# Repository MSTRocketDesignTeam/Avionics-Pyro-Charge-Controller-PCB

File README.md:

# Pyro-Charge-Controller-PCB
KiCAD PCB files of rocket board designed to handle interactions with external pyro charges

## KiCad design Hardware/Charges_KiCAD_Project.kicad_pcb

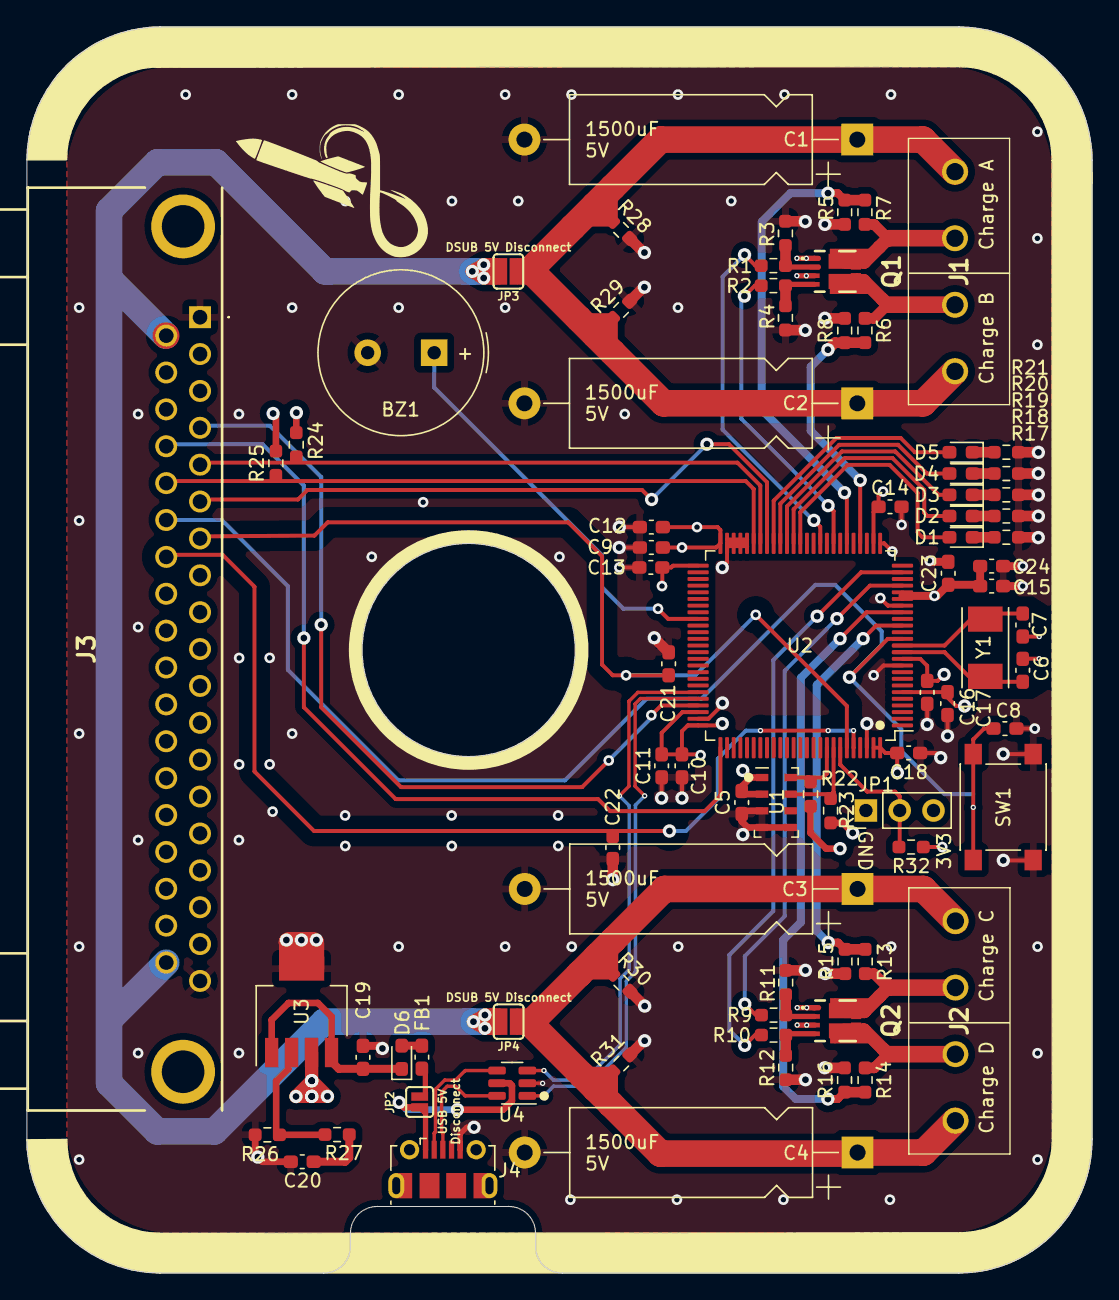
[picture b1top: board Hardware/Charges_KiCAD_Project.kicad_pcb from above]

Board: 4 copper layers, 80.0 x 93.6 mm, 80 parts (0 on the bottom side), 54 nets.

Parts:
BZ1: TP124005-2; Buzzer_TDK_PS1240P02BT_D12.2mm_H6.5mm
C1, C2, C3, C4: 1500uF; CP_Axial_L18.0mm_D6.5mm_P25.00mm_Horizontal
C5, C8, C10, C11, C12, C13, C14, C15, C16, C17, C18, C21, C22: 100nF; C_0603_1608Metric_Pad1.08x0.95mm_HandSolder
C6, C7: 30pF; C_0603_1608Metric_Pad1.08x0.95mm_HandSolder
C9, C20, C23, C24: 1uF; C_0603_1608Metric_Pad1.08x0.95mm_HandSolder
C19: 0.1uF; C_0603_1608Metric_Pad1.08x0.95mm_HandSolder
D1, D3, D5: Red; LED_0603_1608Metric_Pad1.05x0.95mm_HandSolder
D2, D4: Grn; LED_0603_1608Metric_Pad1.05x0.95mm_HandSolder
D6: D_Schottky_Small; D_0603_1608Metric_Pad1.05x0.95mm_HandSolder
FB1: Ferrite_Bead_Small; C_0603_1608Metric_Pad1.08x0.95mm_HandSolder
J1, J2: Terminal Block; TB00250004BE
J3: DB37_Male_MountingHoles; L717SDC37P1ACH4F
J4: 10118192-0001LF; USB_Micro-B_Molex-105017-0001
JP1: Debug Jumper; PinHeader_1x03_P2.54mm_Vertical
JP2: USB 5V Disconnect; SMT-JUMPER_2_NO_SILK
JP3, JP4: DSUB 5V Disconnect; SMT-JUMPER_2_NO_SILK
Q1, Q2: SI7232DN-T1-GE3; SI7232DNT1GE3
R1, R2, R9, R10: 1k; R_0603_1608Metric_Pad0.98x0.95mm_HandSolder
R3, R4, R11, R12, R28, R29, R30, R31: 10k; R_0603_1608Metric_Pad0.98x0.95mm_HandSolder
R5, R6, R13, R14: 100k; R_0603_1608Metric_Pad0.98x0.95mm_HandSolder
R7, R8, R15, R16: 27k; R_0603_1608Metric_Pad0.98x0.95mm_HandSolder
R17, R18, R19, R20, R21: 820; R_0603_1608Metric_Pad0.98x0.95mm_HandSolder
R22, R23, R24, R25, R32: 4.7k; R_0603_1608Metric_Pad0.98x0.95mm_HandSolder
R26: 390; R_0603_1608Metric_Pad0.98x0.95mm_HandSolder
R27: 240; R_0603_1608Metric_Pad0.98x0.95mm_HandSolder
SW1: MCU Reset; SW_SPST_PTS645
U1: MS5607-02BA; LGA-8_3x5mm_P1.25mm
U2: STM32L562VET6Q; LQFP-100_14x14mm_P0.5mm
U3: LP38692MPX-ADJ; SOT-223-5
U4: USBLC6-2SC6; SOT-23-6
Y1: 32MHz; XTAL_ABM7-32.000MHZ-D2Y-T

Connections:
+3V3: C5.2, C9.1, C10.1, C11.1, C12.1, C13.1, C14.1, C15.1, C16.1, C17.1, C18.1, C23.1, C24.1, J3.2, J3.18, JP1.3 (B), R22.2, R23.2, R24.2, R25.2, R32.1, U1.1 (VDD), U1.2 (PS), U2.6 (VBAT), U2.11 (VDD), U2.20 (VREF+), U2.21 (VDDA), U2.27 (VDD), U2.50 (V15SMPS_1), U2.51 (VDD), U2.73 (VDDUSB), U2.75 (VDD), U2.99 (V15SMPS_2), U2.100 (VDD), U3.3 (VOUT)
+5V: C1.1, C2.1, C3.1, C4.1, J1.1, J1.4, J2.1, J2.4, JP3.1 (A), JP4.1 (A), R28.1, R29.1, R30.1, R31.1
/37 Pin DSUB/Alert_Active: J3.6, U2.43 (PE15)
/37 Pin DSUB/Alert_scl: J3.5, R24.1, U2.44 (PB10)
/37 Pin DSUB/Alert_sda: J3.24, R25.1, U2.45 (PB11)
/37 Pin DSUB/DSUB-5V: J3.20, J3.37, JP3.2 (B), JP4.2 (B)
/37 Pin DSUB/Fire: C21.2, J3.7, U2.95 (PB8)
/37 Pin DSUB/Fire_redundant: C22.2, J3.26, U2.96 (PB9)
/37 Pin DSUB/SWCLK: J3.23, U2.76 (PA14)
/37 Pin DSUB/SWDIO: J3.4, U2.72 (PA13)
/Barometer_MS5607/SCLK: R22.1, U1.8 (SCLK), U2.92 (PB6)
/Barometer_MS5607/SDI_SDA: R23.1, U1.7 (SDI/SDA), U2.93 (PB7)
/Fire_A: R1.1, U2.35 (PE7)
/Fire_B: R2.1, U2.33 (PB1)
/Fire_C: R9.1, U2.22 (PA0)
/Fire_D: R10.1, U2.24 (PA2)
/Igniter A: J1.2, Q1.7 (D1_1), Q1.8 (D1_2), Q1.9 (D1_3), Q1.10 (D1_4), Q1.11 (D1_5), Q1.15 (D1_6), R5.1
/Igniter B: J1.3, Q1.5 (D2_1), Q1.6 (D2_2), Q1.12 (D2_3), Q1.13 (D2_4), Q1.14 (D2_5), Q1.16 (D2_6), R6.1
/Igniter C: J2.2, Q2.7 (D1_1), Q2.8 (D1_2), Q2.9 (D1_3), Q2.10 (D1_4), Q2.11 (D1_5), Q2.15 (D1_6), R13.1
/Igniter D: J2.3, Q2.5 (D2_1), Q2.6 (D2_2), Q2.12 (D2_3), Q2.13 (D2_4), Q2.14 (D2_5), Q2.16 (D2_6), R14.1
/MCU L562VET6Q/Buzzer: BZ1.1, U2.59 (PD12)
/MCU L562VET6Q/USB_D+: U2.71 (PA12), U4.1 (IO1)
/MCU L562VET6Q/USB_D-: U2.70 (PA11), U4.3 (IO2)
/MCU L562VET6Q/~RESET: C8.1, J3.25, SW1.1, U2.14 (NRST)
/Sense_A: R5.2, R7.1, U2.31 (PA7)
/Sense_B: R6.2, R8.1, U2.29 (PA5)
/Sense_C: R13.2, R15.1, U2.16 (PC1)
/Sense_D: R14.2, R16.1, U2.18 (PC3)
/USB Connector and ESD/USB_5V: J4.1, JP2.1 (A), U4.5 (VBUS)
/USB Connector and ESD/USB_CONN_D+: J4.3, U4.6 (IO1)
/USB Connector and ESD/USB_CONN_D-: J4.2, U4.4 (IO2)
GND: BZ1.2, C1.2, C2.2, C3.2, C4.2, C5.1, C6.2, C7.2, C8.2, C9.2, C10.2, C11.2, C12.2, C13.2, C14.2, C15.2, C16.2, C17.2, C18.2, C19.2, C20.2, C21.1, C22.1, C23.2, C24.2, J3.1, J3.19, J4.5, JP1.1 (A), Q1.1 (S1), Q1.3 (S2), Q2.1 (S1), Q2.3 (S2), R3.2, R4.2, R7.2, R8.2, R11.2, R12.2, R15.2, R16.2, R17.1, R18.1, R19.1, R20.1, R21.1, R26.2, R28.2, R29.2, R30.2, R31.2, SW1.2, U1.3 (GND), U1.4 (CSB), U1.5 (CSB), U2.10 (VSS), U2.19 (VREF-/VSSA), U2.26 (VSS), U2.46 (VDDSMPS), U2.47 (VLXSMPS), U2.48 (VSSSMPS), U2.49 (VSS), U2.74 (VSS), U2.98 (VSS), U3.5 (GND), U4.2 (GND)
unnamed: C6.1, U2.12 (PH0), Y1.1
unnamed: C7.1, U2.13 (PH1), Y1.2
unnamed: C19.1, D6.1 (K), U3.1 (EN), U3.4 (VIN)
unnamed: C20.1, R27.1
unnamed: D1.1 (K), R17.2
unnamed: D1.2 (A), U2.38 (PE10)
unnamed: D2.1 (K), R18.2
unnamed: D2.2 (A), U2.39 (PE11)
unnamed: D3.1 (K), R19.2
unnamed: D3.2 (A), U2.40 (PE12)
unnamed: D4.1 (K), R20.2
unnamed: D4.2 (A), U2.41 (PE13)
unnamed: D5.1 (K), R21.2
unnamed: D5.2 (A), U2.42 (PE14)
unnamed: D6.2 (A), FB1.1
unnamed: FB1.2, JP2.2 (B)
unnamed: JP1.2 (C), R32.2, U2.94 (PH3)
unnamed: Q1.2 (G1), R1.2, R3.1
unnamed: Q1.4 (G2), R2.2, R4.1
unnamed: Q2.2 (G1), R9.2, R11.1
unnamed: Q2.4 (G2), R10.2, R12.1
unnamed: R26.1, R27.2, U3.2 (ADJ)

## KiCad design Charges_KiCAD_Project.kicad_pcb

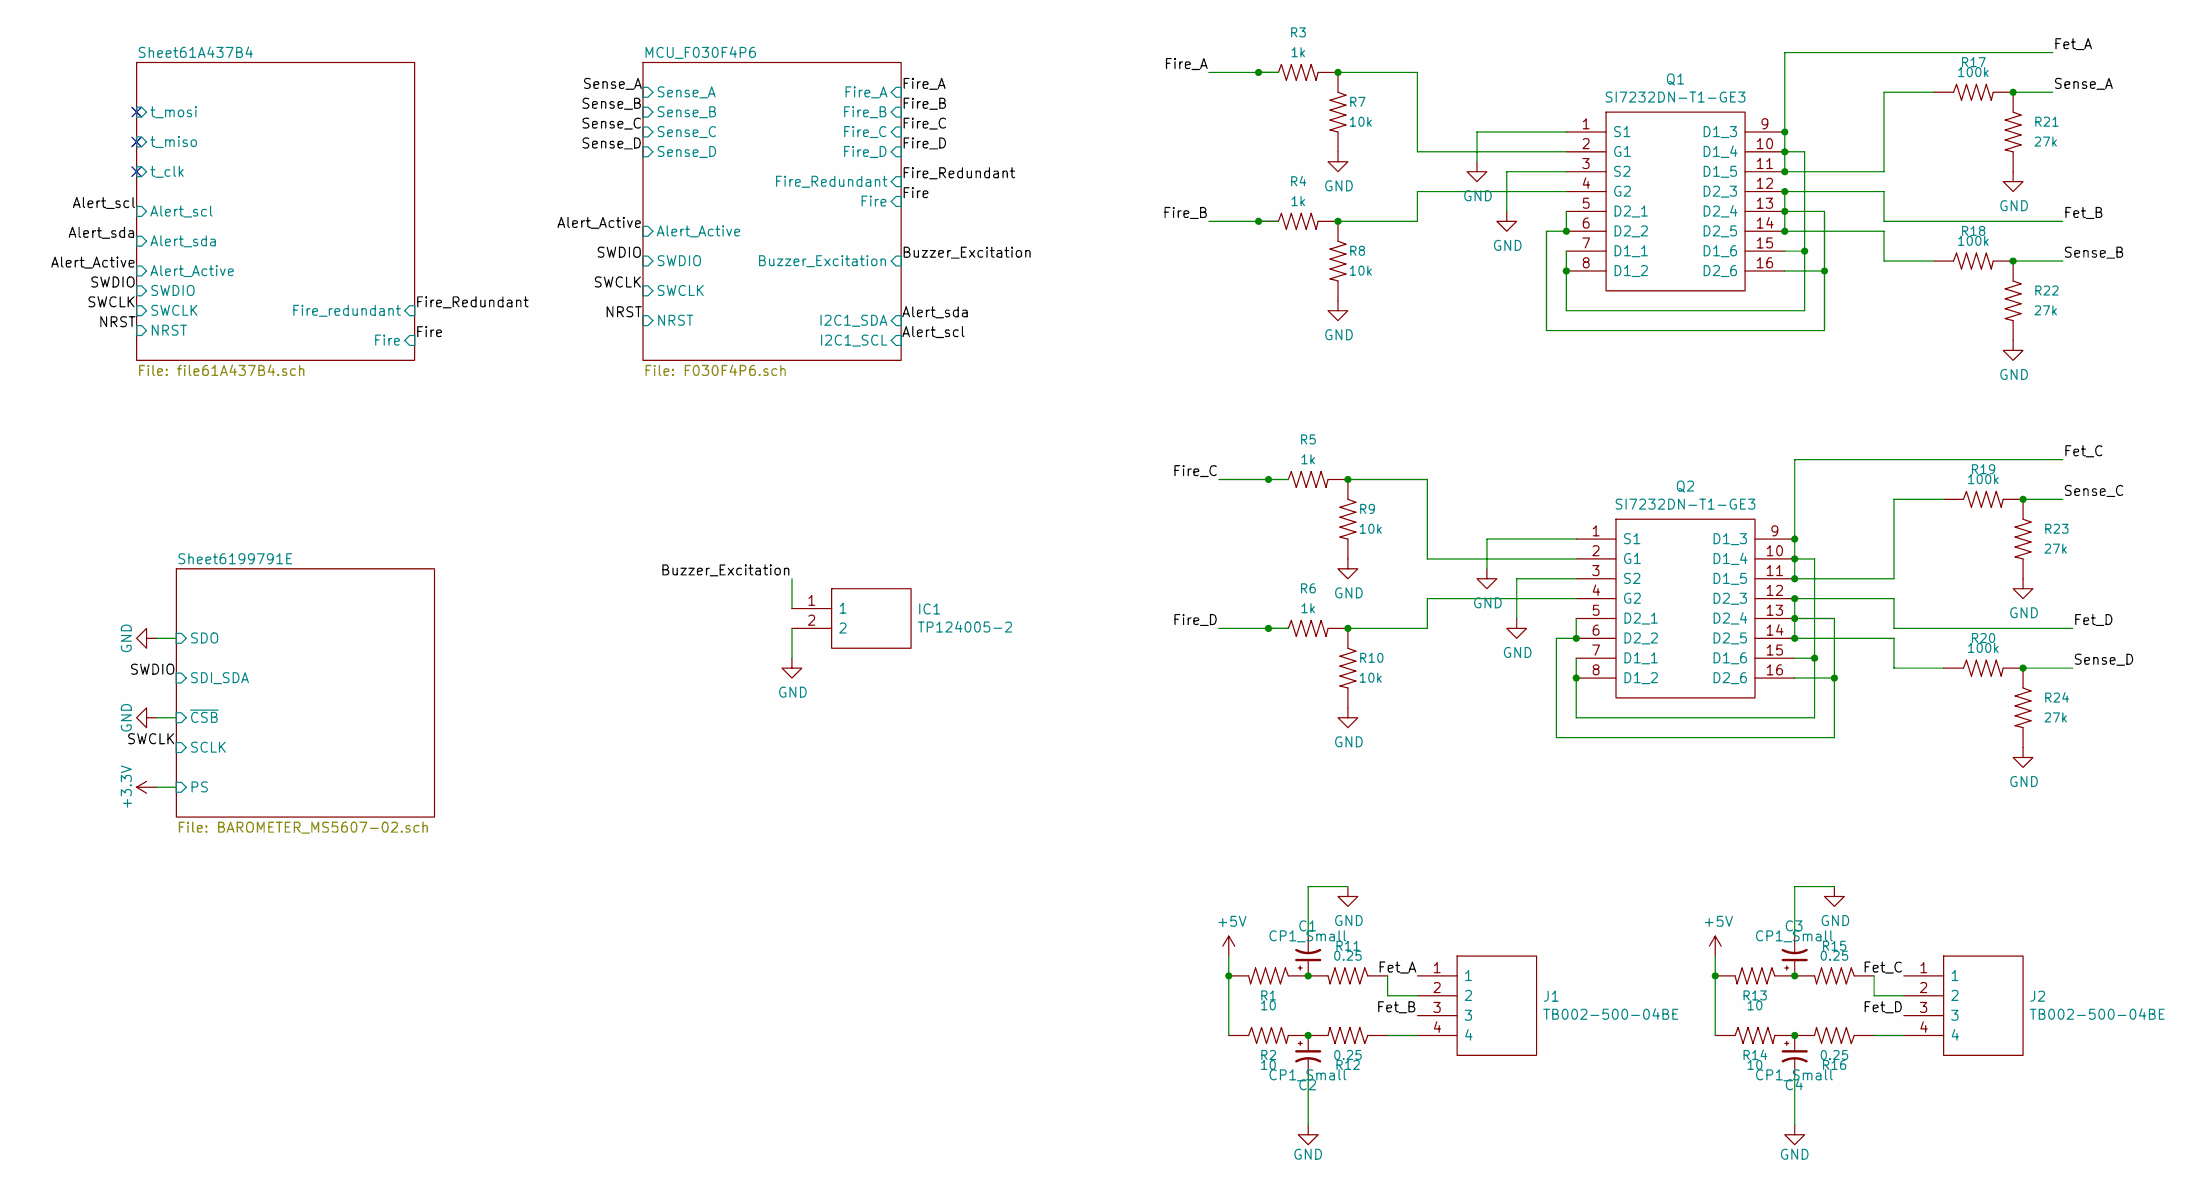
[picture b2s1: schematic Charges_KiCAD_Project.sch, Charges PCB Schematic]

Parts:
C1, C2, C3, C4: CP1_Small; CP_Axial_L10.0mm_D4.5mm_P15.00mm_Horizontal
IC1: TP124005-2; TP1240052; Mouser Part Number 497-TP124005-2
J1, J2: TB002-500-04BE; TB00250004BE; Mouser Part Number 490-TB002-500-04BE
Q1, Q2: SI7232DN-T1-GE3; SI7232DNT1GE3; Mouser Part Number 781-SI7232DN-GE3
R1, R2, R13, R14: 10; R_0603_1608Metric
R3, R4, R5, R6: 1k; R_0603_1608Metric
R7, R8, R9, R10: 10k; R_0603_1608Metric
R11, R12, R15, R16: 0.25; R_0603_1608Metric
R17, R18, R19, R20: 100k; R_0603_1608Metric
R21, R22, R23, R24: 27k; R_0603_1608Metric

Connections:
+5V: R1.2, R2.1, R13.2, R14.1; also elsewhere on the board
/Buzzer_Excitation: IC1.1; also elsewhere on the board
/Fet_A: J1.1, Q1.7 (D1_1), Q1.8 (D1_2), Q1.9 (D1_3), Q1.10 (D1_4), Q1.11 (D1_5), Q1.15 (D1_6), R17.1
/Fet_B: J1.3, Q1.5 (D2_1), Q1.6 (D2_2), Q1.12 (D2_3), Q1.13 (D2_4), Q1.14 (D2_5), Q1.16 (D2_6), R18.1
/Fet_C: J2.1, Q2.7 (D1_1), Q2.8 (D1_2), Q2.9 (D1_3), Q2.10 (D1_4), Q2.11 (D1_5), Q2.15 (D1_6), R19.1
/Fet_D: J2.3, Q2.5 (D2_1), Q2.6 (D2_2), Q2.12 (D2_3), Q2.13 (D2_4), Q2.14 (D2_5), Q2.16 (D2_6), R20.1
/Fire_A: R3.1; also elsewhere on the board
/Fire_B: R4.1; also elsewhere on the board
/Fire_C: R5.1; also elsewhere on the board
/Fire_D: R6.1; also elsewhere on the board
/Sense_A: R17.2, R21.1; also elsewhere on the board
/Sense_B: R18.2, R22.1; also elsewhere on the board
/Sense_C: R19.2, R23.1; also elsewhere on the board
/Sense_D: R20.2, R24.1; also elsewhere on the board
GND: C1.2, C2.2, C3.2, C4.2, IC1.2, Q1.1 (S1), Q1.3 (S2), Q2.1 (S1), Q2.3 (S2), R7.2, R8.2, R9.2, R10.2, R21.2, R22.2, R23.2, R24.2; also elsewhere on the board
unnamed: C1.1, R1.1, R11.2
unnamed: C2.1, R2.2, R12.2
unnamed: C3.1, R13.1, R15.2
unnamed: C4.1, R14.2, R16.2
unnamed: J1.2, R11.1
unnamed: J1.4, R12.1
unnamed: J2.2, R15.1
unnamed: J2.4, R16.1
unnamed: Q1.2 (G1), R3.2, R7.1
unnamed: Q1.4 (G2), R4.2, R8.1
unnamed: Q2.2 (G1), R5.2, R9.1
unnamed: Q2.4 (G2), R6.2, R10.1

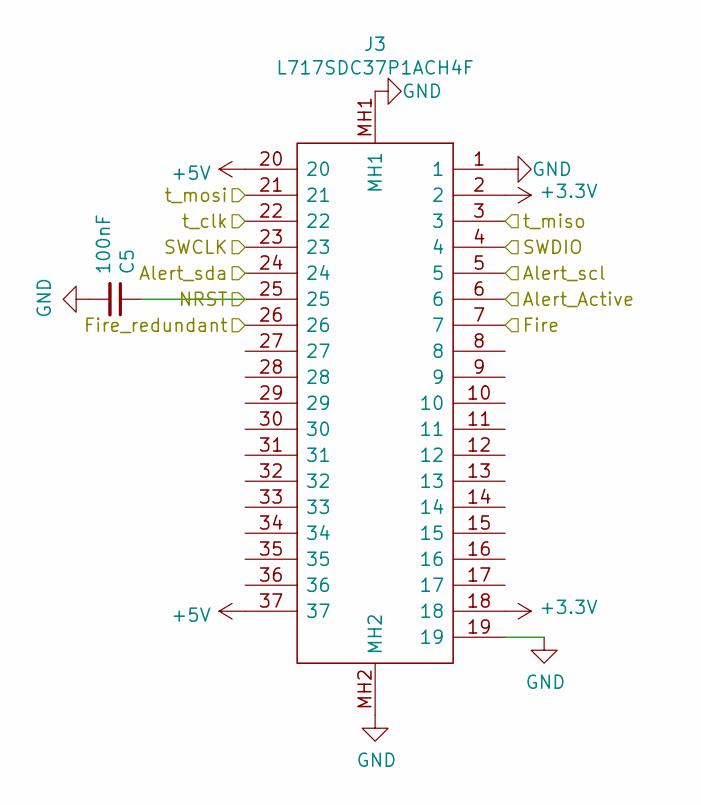
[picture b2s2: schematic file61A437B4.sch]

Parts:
C5: 100nF; C_0603_1608Metric
J3: L717SDC37P1ACH4F; Mouser Part Number 523-L717SDC37P1ACH4F

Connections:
+3V3: J3.2, J3.18; also elsewhere on the board
+5V: J3.20, J3.37; also elsewhere on the board
/Alert_Active: J3.6; also elsewhere on the board
/Alert_scl: J3.5; also elsewhere on the board
/Alert_sda: J3.24; also elsewhere on the board
/Fire: J3.7; also elsewhere on the board
/Fire_Redundant: J3.26; also elsewhere on the board
/NRST: C5.1, J3.25; also elsewhere on the board
/SWCLK: J3.23; also elsewhere on the board
/SWDIO: J3.4; also elsewhere on the board
/Sheet61A437B4/t_clk: J3.22
/Sheet61A437B4/t_miso: J3.3
/Sheet61A437B4/t_mosi: J3.21
GND: C5.2, J3.1, J3.19, J3.MH1, J3.MH2; also elsewhere on the board

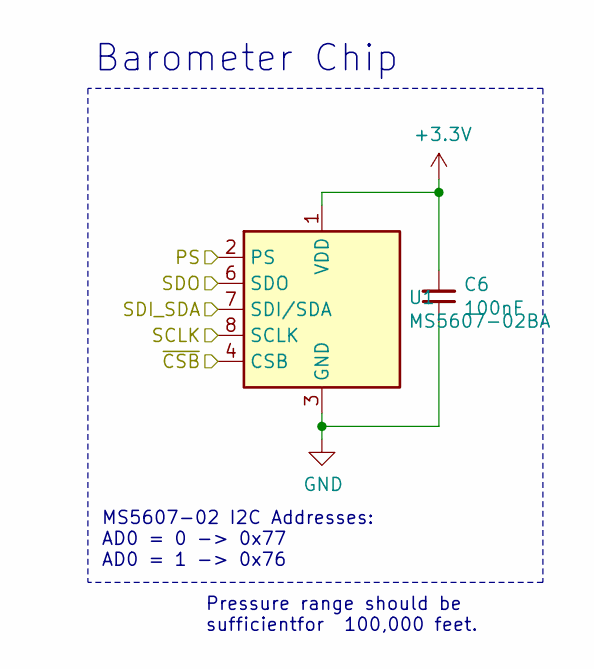
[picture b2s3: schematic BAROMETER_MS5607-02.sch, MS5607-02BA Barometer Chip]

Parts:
C6: 100nF; C_0603_1608Metric
U1: MS5607-02BA; LGA-8_3x5mm_P1.25mm

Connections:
+3V3: C6.2, U1.1 (VDD), U1.2 (PS); also elsewhere on the board
/SWCLK: U1.8 (SCLK); also elsewhere on the board
/SWDIO: U1.7 (SDI/SDA); also elsewhere on the board
GND: C6.1, U1.3 (GND), U1.4 (CSB), U1.5 (CSB), U1.6 (SDO); also elsewhere on the board

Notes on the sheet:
Barometer Chip
MS5607-02 I2C Addresses: AD0 = 0 -> 0x77 AD0 = 1 -> 0x76
Pressure range should be sufficientfor ~ 100,000 feet.

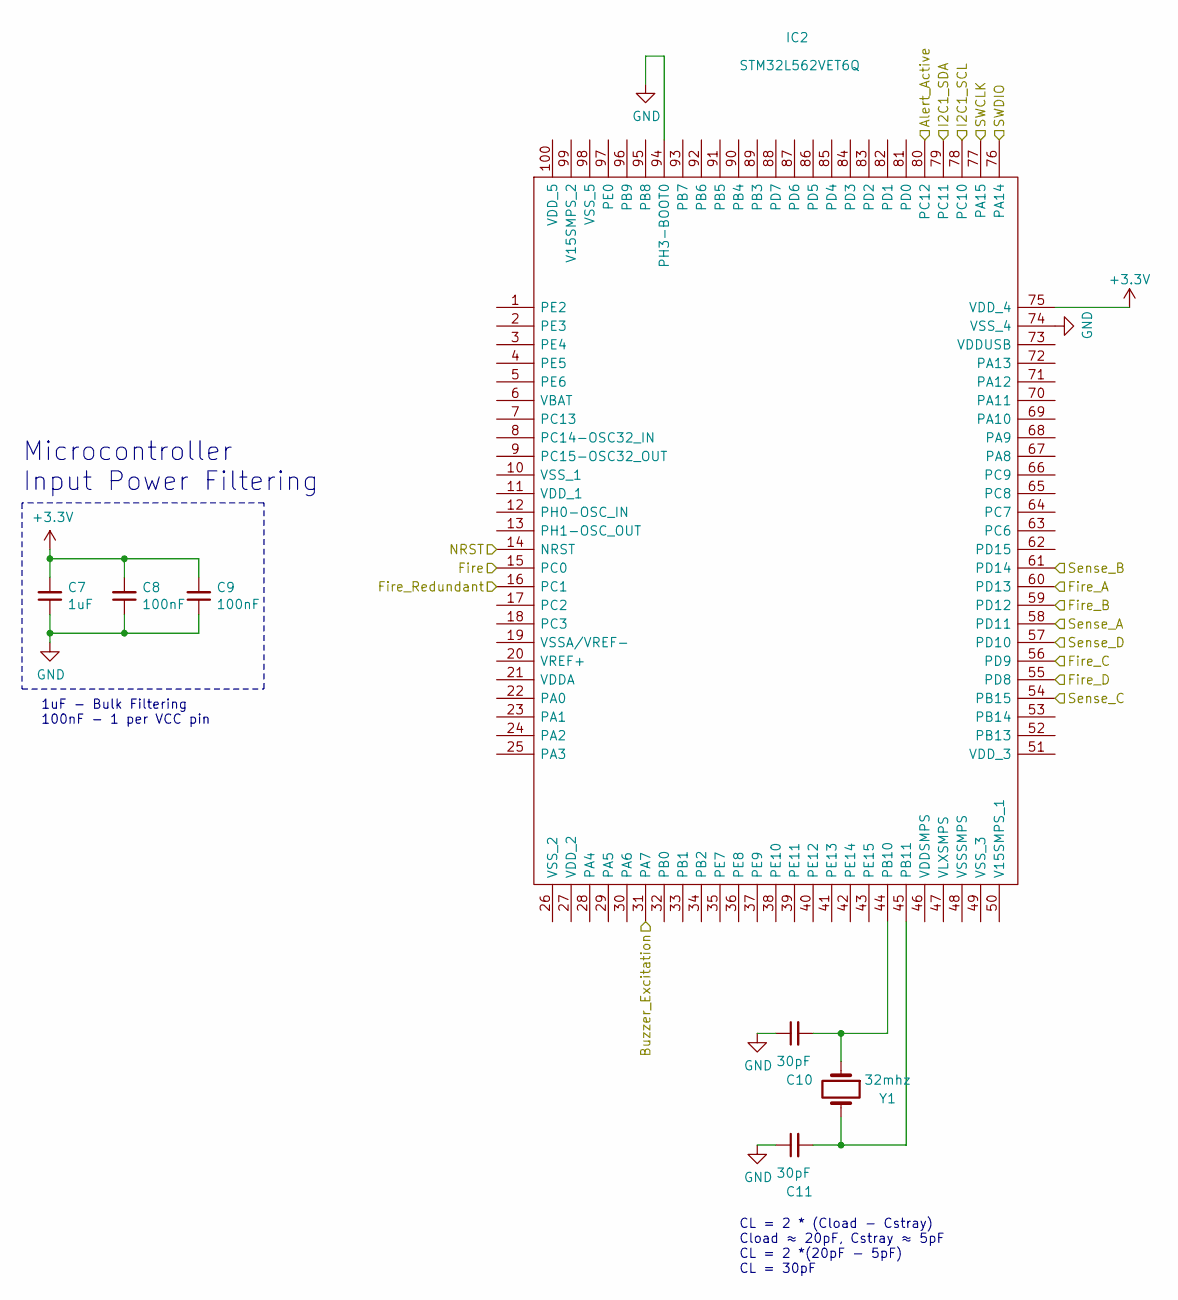
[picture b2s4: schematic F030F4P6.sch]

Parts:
C7: 1uF; C_0603_1608Metric
C8, C9: 100nF; C_0603_1608Metric
C10, C11: 30pF; C_0603_1608Metric
IC2: STM32L562VET6Q; QFP50P1600X1600X160-100N; Mouser Part Number 511-STM32L562VET6Q
Y1: 32mhz; Crystal_HC49-4H_Vertical

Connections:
+3V3: C7.2, C8.2, C9.2, IC2.75 (VDD_4); also elsewhere on the board
/Alert_Active: IC2.80 (PC12); also elsewhere on the board
/Alert_scl: IC2.78 (PC10); also elsewhere on the board
/Alert_sda: IC2.79 (PC11); also elsewhere on the board
/Buzzer_Excitation: IC2.31 (PA7); also elsewhere on the board
/Fire: IC2.15 (PC0); also elsewhere on the board
/Fire_A: IC2.60 (PD13); also elsewhere on the board
/Fire_B: IC2.59 (PD12); also elsewhere on the board
/Fire_C: IC2.56 (PD9); also elsewhere on the board
/Fire_D: IC2.55 (PD8); also elsewhere on the board
/Fire_Redundant: IC2.16 (PC1); also elsewhere on the board
/NRST: IC2.14 (NRST); also elsewhere on the board
/SWCLK: IC2.77 (PA15); also elsewhere on the board
/SWDIO: IC2.76 (PA14); also elsewhere on the board
/Sense_A: IC2.58 (PD11); also elsewhere on the board
/Sense_B: IC2.61 (PD14); also elsewhere on the board
/Sense_C: IC2.54 (PB15); also elsewhere on the board
/Sense_D: IC2.57 (PD10); also elsewhere on the board
GND: C7.1, C8.1, C9.1, C10.1, C11.1, IC2.74 (VSS_4), IC2.94 (PH3-BOOT0); also elsewhere on the board
unnamed: C10.2, IC2.44 (PB10), Y1.1
unnamed: C11.2, IC2.45 (PB11), Y1.2

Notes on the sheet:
CL = 2 * (Cload - Cstray) Cload ≈ 20pF, Cstray ≈ 5pF CL = 2 *(20pF - 5pF) CL = 30pF
1uF - Bulk Filtering 100nF - 1 per VCC pin
Microcontroller Input Power Filtering

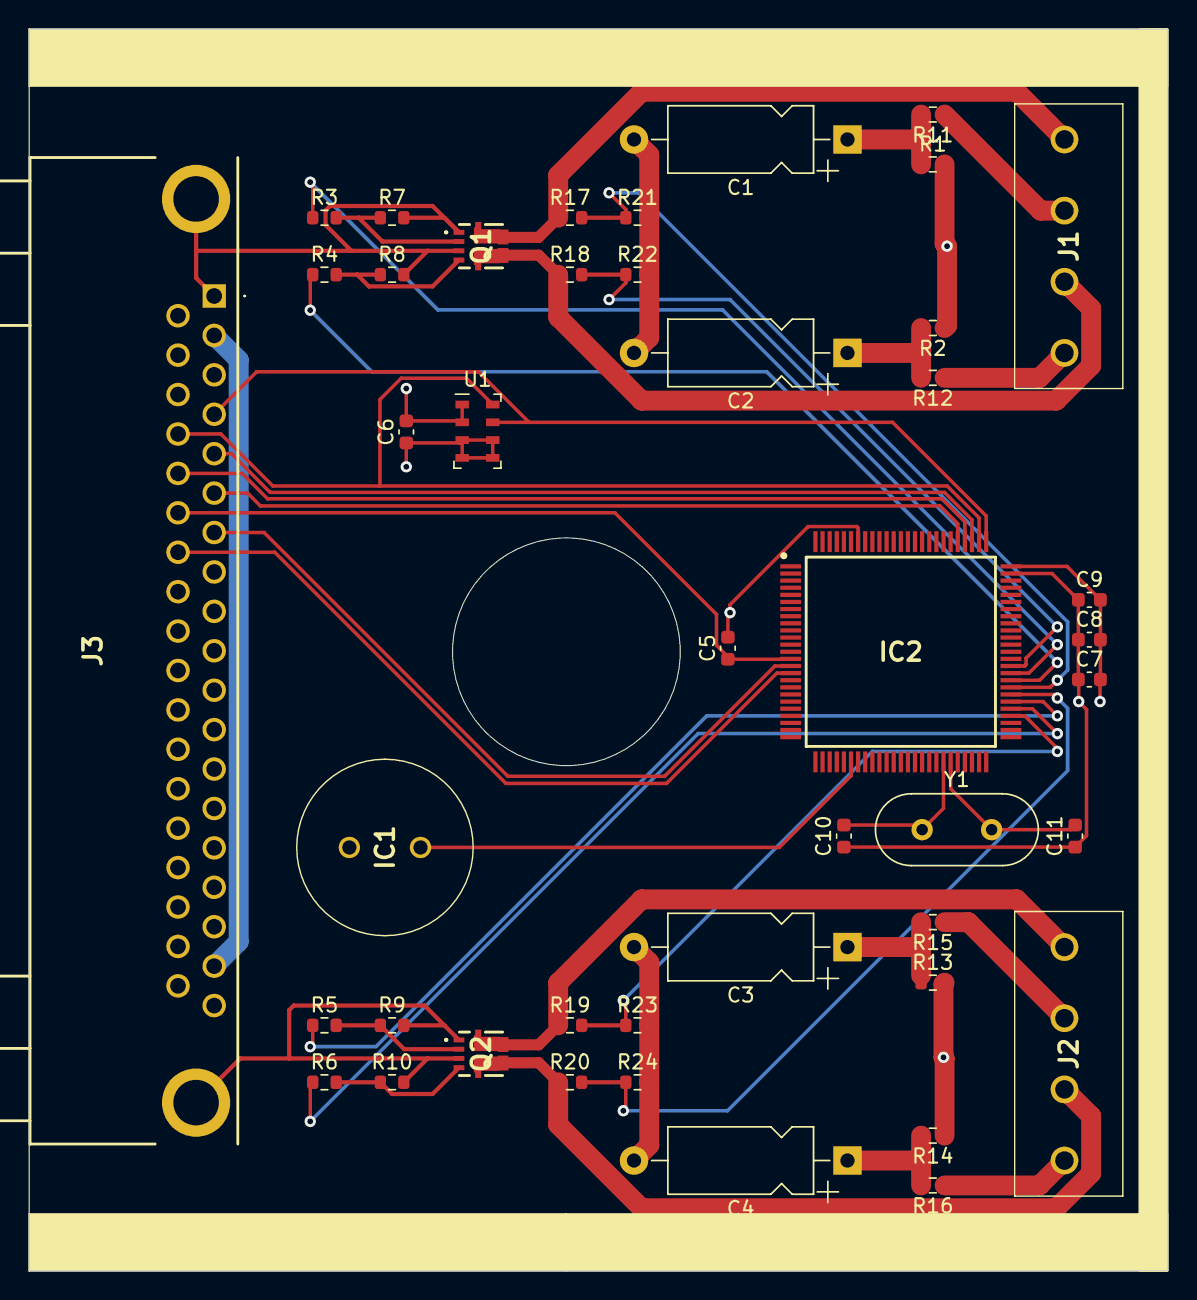
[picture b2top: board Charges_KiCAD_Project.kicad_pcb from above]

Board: 4 copper layers, 80.0 x 87.2 mm, 44 parts (0 on the bottom side), 38 nets.

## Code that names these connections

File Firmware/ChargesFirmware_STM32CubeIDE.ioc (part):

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Mcu.Name=STM32L562VETxQ
Mcu.Package=LQFP100
Mcu.UserName=STM32L562VETxQ
PA11.Mode=Device
PA11.Signal=USB_DM
PA12.Mode=Device
PA12.Signal=USB_DP
PA13\ (JTMS/SWDIO).Mode=Serial_Wire
PA13\ (JTMS/SWDIO).Signal=DEBUG_JTMS-SWDIO
PA14\ (JTCK/SWCLK).Mode=Serial_Wire
PA14\ (JTCK/SWCLK).Signal=DEBUG_JTCK-SWCLK
PB6.Mode=I2C
PB6.Signal=I2C1_SCL
PB7.Mode=I2C
PB7.Signal=I2C1_SDA
PD12.Signal=S_TIM4_CH1
PE14.Signal=GPIO_Output
PH0-OSC_IN\ (PH0).Mode=HSE-External-Oscillator
PH0-OSC_IN\ (PH0).Signal=RCC_OSC_IN
PH1-OSC_OUT\ (PH1).Mode=HSE-External-Oscillator
PH1-OSC_OUT\ (PH1).Signal=RCC_OSC_OUT
RCC.HSE_VALUE=32000000
RCC.SYSCLKFreq_VALUE=96000000
RCC.SYSCLKSource=RCC_SYSCLKSOURCE_PLLCLK
board=custom

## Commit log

2021-09-30 Create LICENSE
2021-11-03 Actually made the boards
    Boards have been made
2021-11-17 Board update
    Added capacitors and extra charge stuff
2021-11-24 Edit to bus
    Bus changed as well as some other things to almost finish it up
2021-11-24 Change to bus
    oopsie on one of the bus pins
2021-11-29 Updated PCB
    Finalized most of the charges board and PCB
2021-11-29 FIx to Via
    Via was too close to a track according to utility. It was moved a bit over.
2021-11-29 Fix to components
    Changed the buzzer and terminal blocks
2021-11-30 updated pcb
    pcb updated to the right size
2021-11-30 Updated PCB
    pcb dimensions were a little off on the silk so that was updated
2021-11-30 added gerber files
    gerber files added
2021-11-30 updated traces
    trace widths were updated
2021-11-30 updated pcb
    pcb wasnt fully aligned. that is now fixed
2021-12-01 updated board
    updated the board again
    added a crystal
2021-12-05 Changes to PCB
    noticed that 3v3 plane only had like 2 connections, so i changed it to a mixed with mainly 5v instead
2021-12-06 Reformatted repo
2021-12-10 Changes to PCB size and components
    PCB size was changed by adding 3mm to the top and bottom, the screw terminal was switched to a 90 degree angle one, and the libraries were updated
2021-12-21 Replaced passive component footprints with handsolder variants
    Most components unaffected, redesign was needed around SI7232DN chips
2021-12-21 Component sheets updated
    Component sheets were added from the telemetry board to match across all boards
2021-12-21 deleting redundant project.
    Project didnt need to be in this folder
2022-01-16 update to caps and board layout
    caps were changed and resistors were removed as they were not needed
2022-01-18 Added qr codes and fixed silk screen
    Qr code was added and the silk screens were fixed. corners were also rounded
2022-01-25 Added signatures to silkscreen
2022-02-04 replaced caps footprint
    footprint for cap was changed and copper pours were on on the top and the bottom
2022-02-04 updated caps
    finished update on cap footprints
2022-02-05 updated traces
    moved traces further away from the center hole
2022-02-05 ignoring backups
    added line to gitignore to ignore the backups on kicad
2022-02-05 Corrected 3D models for buzzer, terminals, mosfets, and mcu
2022-02-07 Added correct crystal for mcu, re-routing of data lines in progress
2022-02-07 Routed Alert I2C lines
2022-02-07 Routed all traces and components, need to place LEDs
2022-02-07 All traces routed
2022-02-07 Added 3D models for USB components
    USB Voltage Regulator chip still needs corrected footprint/pinout
2022-02-07 Realigned pcb grid, added QR code to silkscreen
2022-02-07 Added stitching vias to ground pours
2022-02-07 Adjusted silkscreen labels
2022-02-07 corrected voltage regulator footprint
2022-02-08 Added bleed off resistors to charge capacitors
    R = -t/C*ln(V/Vo) = (-1)/(0.0015)*ln(1v/5v) = 1072.96 ≈ 1000 ohm
2022-02-08 Aligned center hole
2022-02-08 Replaced .wrl models with .step
2022-02-12 Added cutout for USB connector, moved terminal blocks inwards
    Terminal blocks need correct right angle 3D model
2022-02-13 Adjusted center hole position
2022-02-13 Adjusted position of DSUB connector
2022-02-13 Adjusted center hole silkscreen
2022-02-21 Updated hole location
    Hole was moved 2mm to the left to fit tolerances
2022-02-27 Updated .gitignore
2022-02-28 Corrected edge cuts, aligned silkscreen border, aligned all components, aligned grid/drill origin, aligned center hole
    Some traces need to be corrected around the center hole
2022-02-28 Corrected board dimension labels
2022-03-05 Adjusted silkscreen labels, corrected MCU pinout, added pull up resistor to bootloader line, added usb cut out
2022-03-07 Adjusted silkscreen
2022-03-08 Moved USB inwards to increase clearance to housing
2022-03-18 Generated Gerb
    Gerb and drill files were generated
2022-04-24 Added STM32CubeIDE Firmware project
2022-05-26 Code for beeping and basic i2c
    starting code for beeping and i2c for the charges board. Still needs a lot of work
2022-05-27 progress on MS5607 code
2022-05-27 ready to test MS5607
2022-05-27 Fixed issues with functions
    Had to go into the ioc to check visibility on the two functions that had errors. doing so fixed the issue however the code functionality is still unknown
2022-05-27 Added Type Casting
2022-06-05 updated firmware
    updated firmware to try and get i2c to work
